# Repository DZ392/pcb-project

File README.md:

# pcb-project

🦋 Butterfly USB Hub Dongle

This is a small 4-port USB hub built into a butterfly-shaped PCB. Instead of using a cable like most USB hubs, it plugs directly into the side of a laptop.

I wanted to make something a more compact usb that can be used for anything I need, so I designed mine as a dongle and I wanted it to work with newer laptops that mostly use USB-C as well as older ones that still have USB-A.

The board has a male USB-C connector and a male USB-A connector for the laptop side. You only use one of them at a time depending on what port your laptop has.

I also wanted the PCB itself to be part of the design rather than just a rectangular board, so I shaped it like a butterfly and plan to add a UV-printed gradient design to it as a challenge. 

The PCB is 1.2 mm thick to work with the edge-mount USB connectors.

Why I Made It

I use devices with both USB-A and USB-C, and I thought it would be useful to have one small hub that could plug into either type of laptop without needing another adapter or cable. I also wanted to try designing my first PCB for practice. 

I started by following the Macondo USB hub tutorial to understand how a USB hub circuit works. From there, I changed the design, I added both USB-C and USB-A upstream connectors, changed it into a direct-plug dongle, designed the butterfly-shaped PCB, and added my own visual design.

This project has also helped to learn KiCad and understand how the schematic, PCB layout, footprints, connectors, and physical board shape all have to work together.

How to Use It

1. Plug either the USB-C or USB-A connector into your laptop. Only one should be connected at a time.
2. Plug USB-A devices into the three USB-A ports on the board.
3. A USB-C device can also be connected to the USB-C port on the hub.

* Hub IC: CoreChips SL2.1S
* USB standard: USB 2.0
* Upstream: 1 × male USB-C + 1 × male USB-A
* Downstream: 3 × female USB-A + 1 × female USB-C
* PCB: 2-layer, 1.2 mm thick
* Size: about 75 mm × 65 mm
* Board shape: custom butterfly
* External power: not required

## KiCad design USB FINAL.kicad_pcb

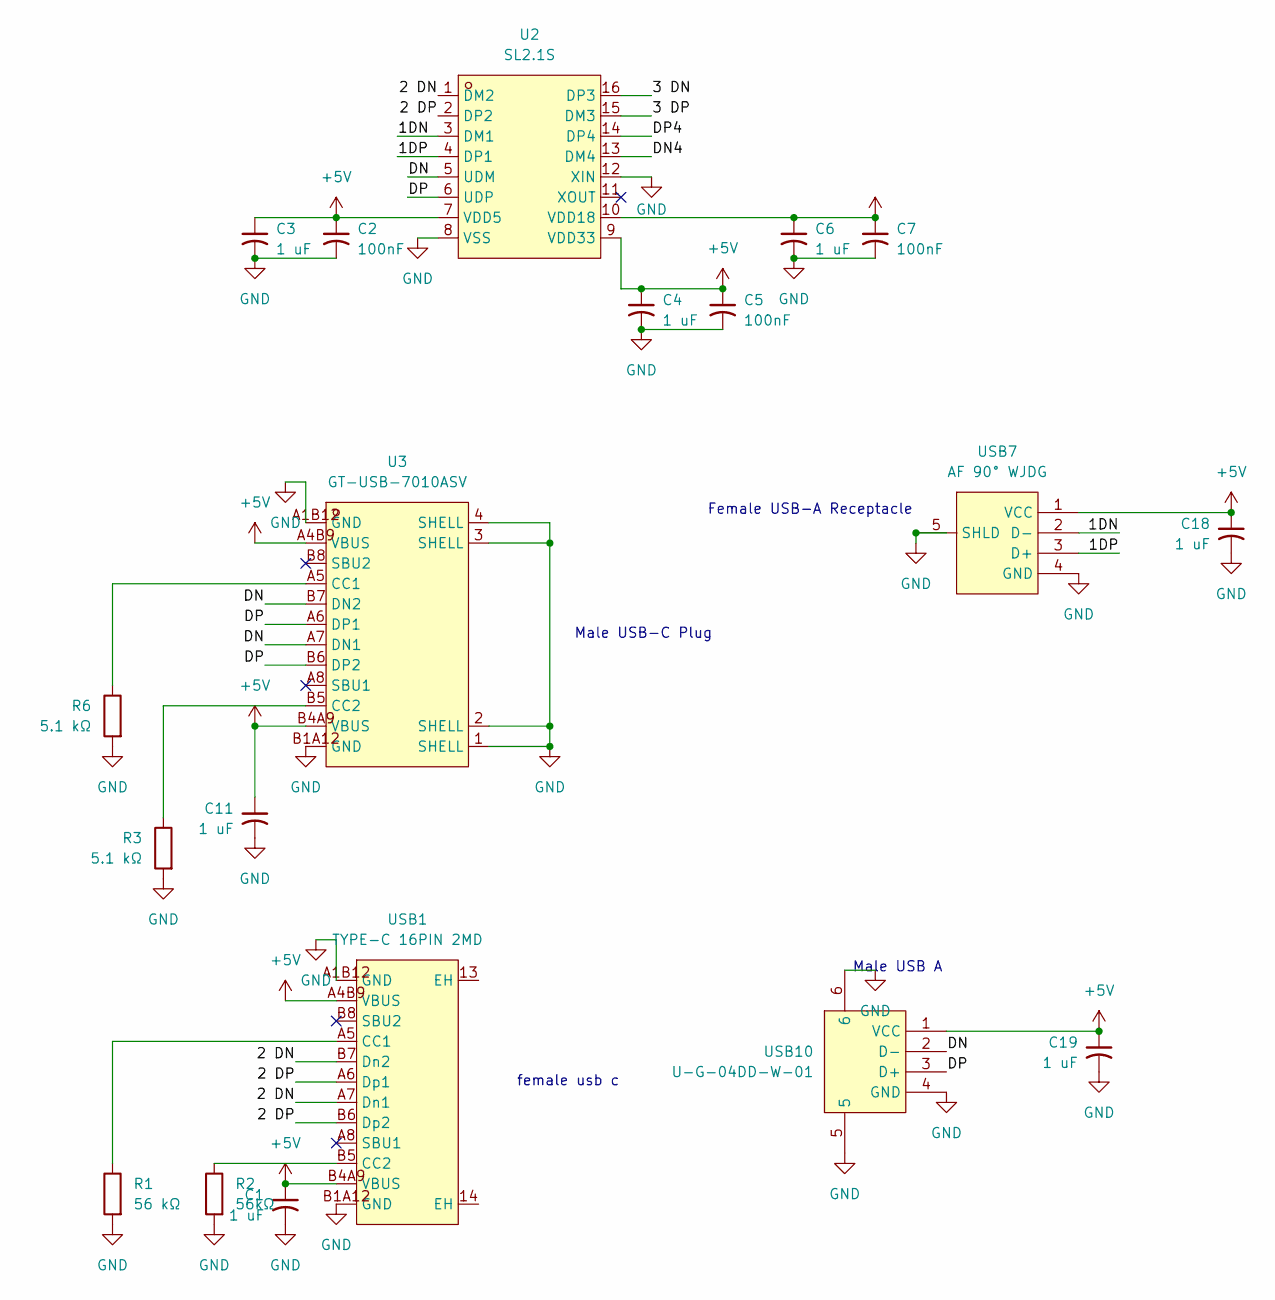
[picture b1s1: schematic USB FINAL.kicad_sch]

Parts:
C1, C3, C4, C6, C11, C18, C19: 1 uF; C_0805_2012Metric_Pad1.18x1.45mm_HandSolder
C2, C5, C7: 100nF; C_0805_2012Metric_Pad1.18x1.45mm_HandSolder
R1: 56 kΩ; R_0805_2012Metric_Pad1.20x1.40mm_HandSolder
R2: 56kΩ; R_0805_2012Metric_Pad1.20x1.40mm_HandSolder
R3, R6: 5.1 kΩ; R_0805_2012Metric_Pad1.20x1.40mm_HandSolder
U2: SL2.1S; SSOP-16_L4.6-W2.6-P0.53-LS4.0-BL; MPN SL2.1s; LCSC Part C2684433
U3: GT-USB-7010ASV; USB-C-SMD_G-SWITCH_GT-USB-7010ASV; MPN GT-USB-7010ASV; LCSC Part C2988369
USB1: TYPE-C 16PIN 2MD; USB-C-SMD_TYPE-C-16PIN-2MD-073; MPN TYPE-C 16PIN 2MD(073); LCSC Part C2765186
USB7: AF 90° WJDG; USB-A-TH_AF-WJDG; MPN AF 90° WJDG; LCSC Part C456018
USB10: U-G-04DD-W-01; USB-A-TH_U-G-04WD-W-01; MPN U-G-O4DD-W-1; LCSC Part C98125

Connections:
+5V: C1.1, C2.1, C3.1, C4.1, C5.1, C6.1, C7.1, C11.1, C18.1, C19.1, U2.7 (VDD5), U2.9 (VDD33), U2.10 (VDD18), U3.A4B9 (VBUS), U3.B4A9 (VBUS), USB1.A4B9 (VBUS), USB1.B4A9 (VBUS), USB7.1 (VCC), USB10.1 (VCC)
/1DN: U2.3 (DM1), USB7.2 (D-)
/1DP: U2.4 (DP1), USB7.3 (D+)
/2 DN: U2.1 (DM2), USB1.A7 (Dn1), USB1.B7 (Dn2)
/2 DP: U2.2 (DP2), USB1.A6 (Dp1), USB1.B6 (Dp2)
/3 DN: U2.16 (DP3)
/3 DP: U2.15 (DM3)
/DN: U2.5 (UDM), U3.A7 (DN1), U3.B7 (DN2), USB10.2 (D-)
/DN4: U2.13 (DM4)
/DP: U2.6 (UDP), U3.A6 (DP1), U3.B6 (DP2), USB10.3 (D+)
/DP4: U2.14 (DP4)
GND: C1.2, C2.2, C3.2, C4.2, C5.2, C6.2, C7.2, C11.2, C18.2, C19.2, R1.2, R2.2, R3.2, R6.2, U2.8 (VSS), U2.12 (XIN), U3.1 (SHELL), U3.2 (SHELL), U3.3 (SHELL), U3.4 (SHELL), U3.A1B12 (GND), U3.B1A12 (GND), USB1.A1B12 (GND), USB1.B1A12 (GND), USB7.4 (GND), USB7.5 (SHLD), USB10.4 (GND), USB10.5, USB10.6
unnamed: R6.1, U3.A5 (CC1)
unnamed: R3.1, U3.B5 (CC2)
unnamed: R1.1, USB1.A5 (CC1)
unnamed: R2.1, USB1.B5 (CC2)

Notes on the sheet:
Male USB-C Plug
female usb c
Female USB-A Receptacle
Male USB A

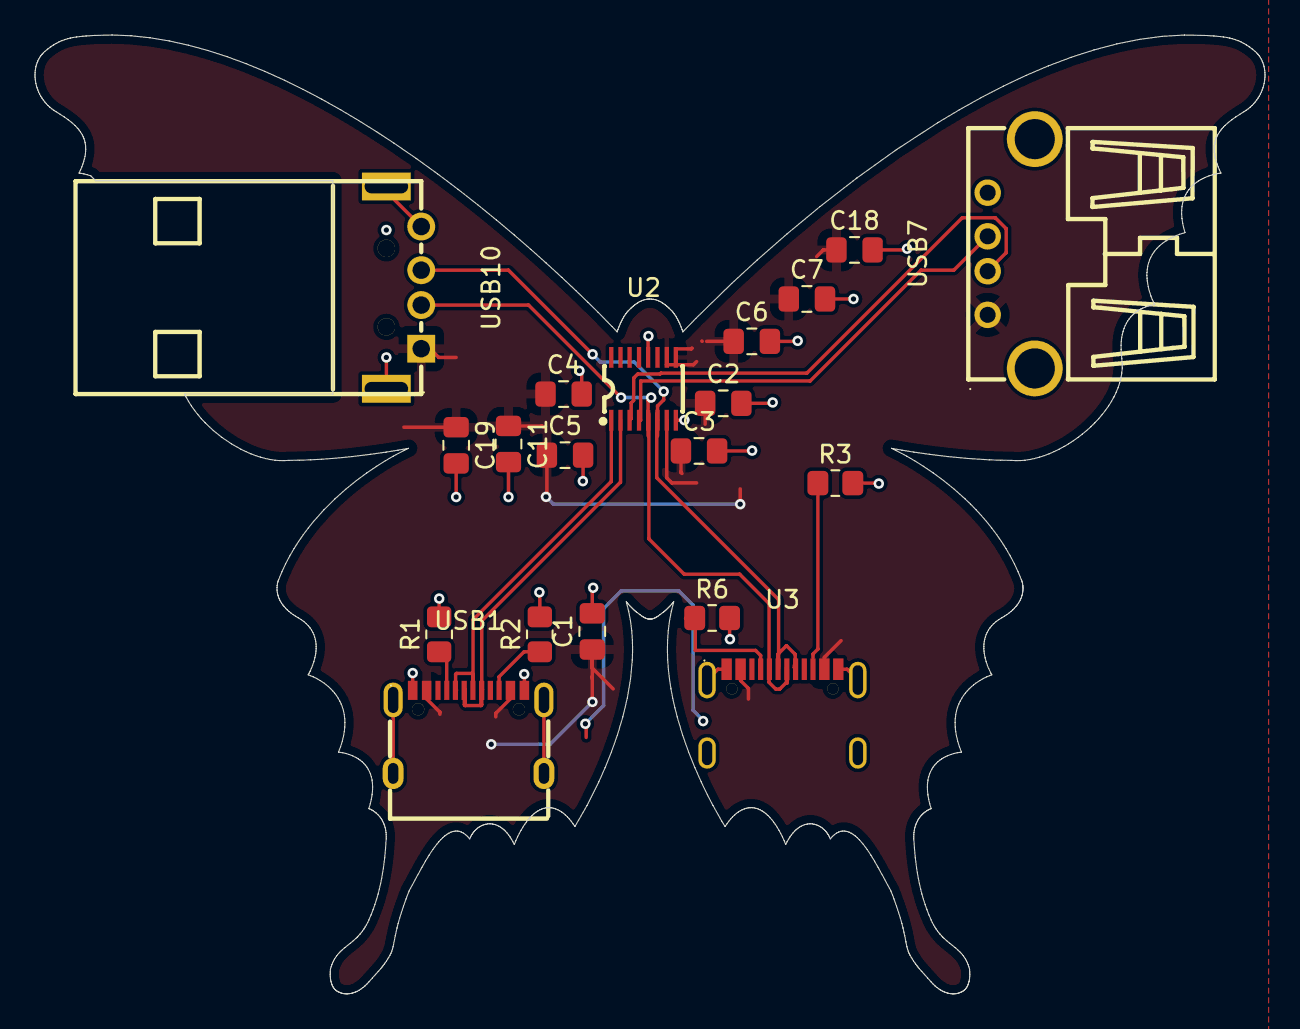
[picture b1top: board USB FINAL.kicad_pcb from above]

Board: 2 copper layers, 70.5 x 55.0 mm, 19 parts (0 on the bottom side), 12 nets.
